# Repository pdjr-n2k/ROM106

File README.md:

# ROM106 - NMEA 2000 relay output module

**ROM106** is a specialisation of
[NOP100](https://github.com/preeve9534/NOP100)
and implements a six channel NMEA 2000 relay output module which
presents on the host NMEA bus as a switchbank device with Class
Code 30 (Electrical Distribution) and Function Code 140 (Load
Controller).

The module transmits PGN 127501 Binary Status Report messages and
responds to PGN 127502 Switch Bank Control messages addressed to
the module's instance number.

The module is powered from the host NMEA bus and has an LEN of 0.5.

## Relay outputs

**ROM106**'s relay output sub-system consists of six bistable relays
with zero-volt common (CO), normally-open (NO) and normally-closed (NC)
terminals availble for the connection of external circuits.

Relay connections are rated for a maximum of 5A at up to 220VAC
or 30VDC.

## Relay operation and status reporting

**ROM106** accepts PGN 127502 Switch Bank Control messages addressed
to its module's instance number, updating its relay outputs to the
requested states.
Operation of individual relays is queued so that any request for state
change of multiple relays cannot result in a possibly problematic
concurrent relay switching load.

The module reports module status by regularly broadcasting a PGN 127501
Binary Status Report message.
Additionally, a report is broadcast immediately following the receipt and
handling of a PGN 127502 Switch Bank Control message.
The regular transmission interval can be configured by the user.

## Module configuration

**ROM106** understands the following configuration parameters.

| Address | Name                         | Default value | Description |
| :---:   | :---                         | :---:         | :--- |
| 0x01    | MODULE INSTANCE NUMBER       | 0xFF          | Used as a unique identifier for this switchbank. Must be set by the user to a value between 0 and 252 before the module will transmit status reports. |
| 0x02    | PGN 127501 TRANSMIT INTERVAL | 0x04          | Sets the basic transmit interval for broadcast of module status reports.|

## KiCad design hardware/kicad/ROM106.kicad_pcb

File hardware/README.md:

# TSENSE 1.0 Prototype Hardware

This microcontroller-based design uses just a handful of components
to implement an 8-channel NMEA 2000 temperature sensor module which
is powered from the host NMEA 2000 bus and draws around 50mA of
current at a nominal 12VDC with all eight sensor channels in use.
This equates to an NMEA bus load of less that 1 LEN.

The module supports
[National Semiconductor LM335Z](https://www.switchelectronics.co.uk/pub/media/pdf/LM335Z.pdf)
precision temperature sensors connected through a two-wire interface.
The module cannot be used with resistance or current-loop sensors.

The module has a simple user configuration interface consisting of a
DIP switch, momentary push-button and LED outputs.
A separate LED indicates module operating state.

## Active components

| Element         | Device |
|:----------------|:-------|
| MCU             | [Teensy 3.2](https://www.pjrc.com/store/teensy32.html) |
| Power supply    | [Traco Power TMR 1-1211](https://tracopower.com/tmr1-datasheet/) |
| CAN transceiver | [MicroChip MCP2551](http://ww1.microchip.com/downloads/en/devicedoc/21667e.pdf) |

## Schematic design

<br clear="both"/>

## Physical design

The prototype module uses through-hole components on a 75mm square PCB
mounted in a flanged ABS enclosure.
The enclosure is machined to accommodate an NMEA cable connector and
a single 3mm LED indicator.

| Element         | Device |
|:----------------|:-------|
| Enclosure       | [RS 919-0357](https://docs.rs-online.com/960c/0900766b814af9a1.pdf) |
| NMEA connector  | [M12 5-pin connector](https://docs.rs-online.com/e3ad/0900766b8152901f.pdf) |

<br clear="both"/>

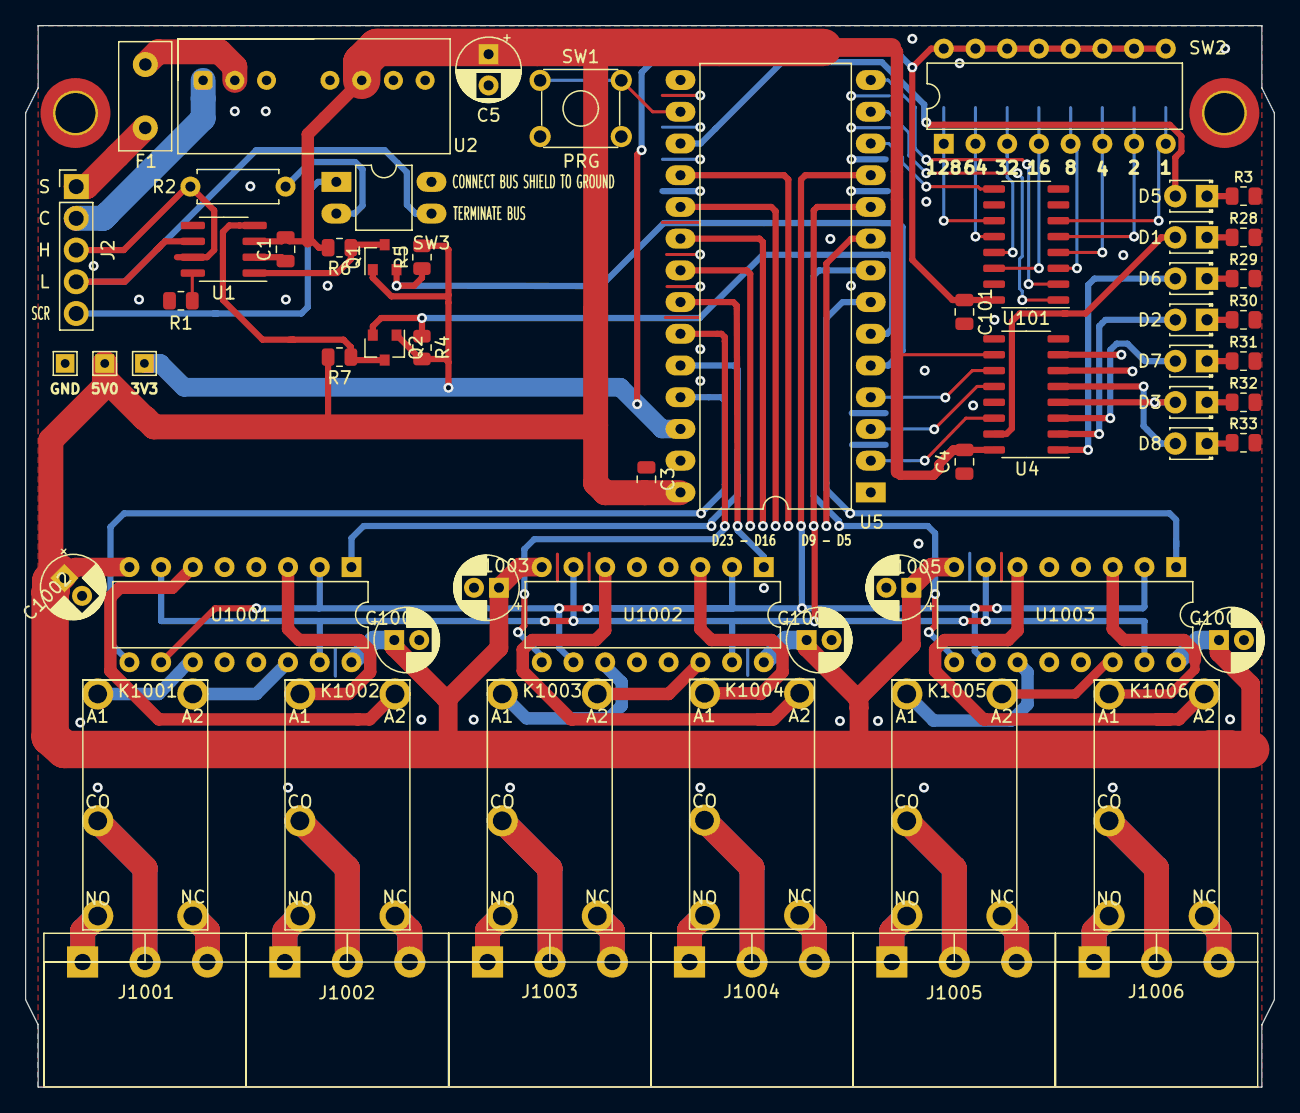
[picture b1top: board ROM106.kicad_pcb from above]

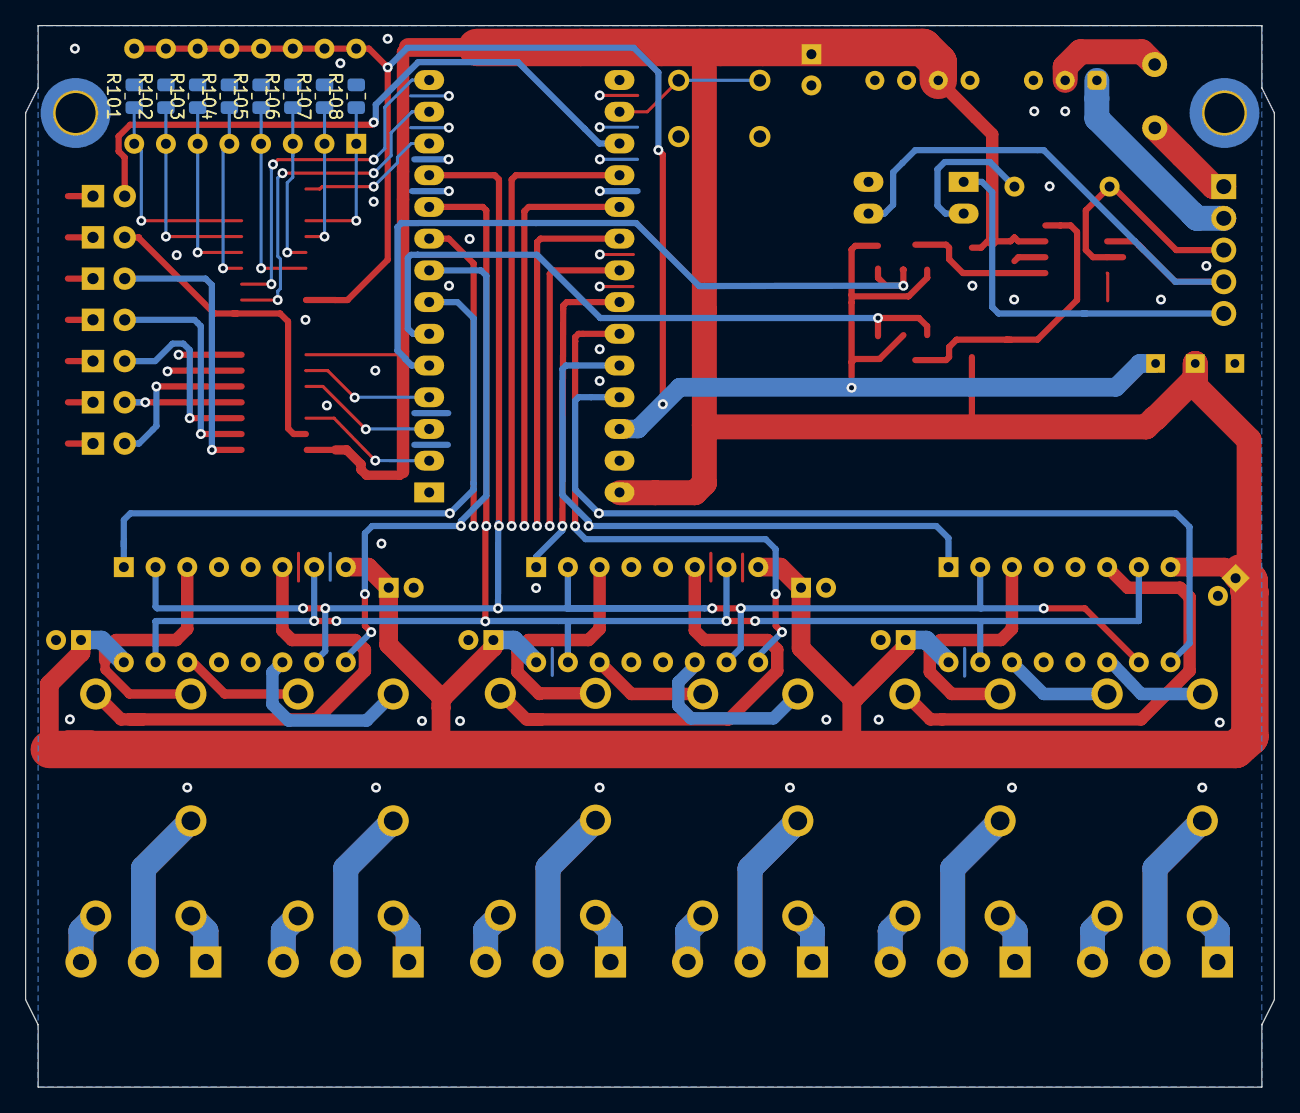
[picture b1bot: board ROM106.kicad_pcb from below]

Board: 2 copper layers, 100.0 x 85.0 mm, 68 parts (8 on the bottom side), 82 nets.

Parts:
C1, C3, C4, C101: 100nF; C_0805_2012Metric
C5: 100nF; CP_Radial_D5.0mm_P2.50mm
C1001, C1002, C1003, C1004, C1005, C1006: 100nF; CP_Radial_D5.0mm_P2.00mm
D1, D2, D3, D5, D6, D7, D8: LED; LED_D1.8mm_W3.3mm_H2.4mm
F1: 1A; Fuse_Littelfuse_395Series
J2: CAN; PinHeader_1x05_P2.54mm_Vertical
J1001, J1002, J1003, J1004, J1005, J1006: Screw_Terminal_01x03; 8971187_3_PIN_5MM_PLUGGABLE_HEADER
K1001, K1002, K1003, K1004, K1005, K1006: PE014F05
Q1, Q2: BSS138; SOT-23
R1, R101, R102, R103, R104, R105, R106, R107, R108: 4K7 0.125W; R_0805_2012Metric
R2: 120R 0.5W; R_Axial_DIN0207_L6.3mm_D2.5mm_P7.62mm_Horizontal
R3, R28, R29, R30, R31, R32, R33: 560R; R_0805_2012Metric
R4, R5, R6, R7: 10K 0.125W; R_0805_2012Metric
SW1: PRG; SW_TH_Tactile_Omron_B3F-10xx
SW2: INSTANCE; DIP-16_W7.62mm
SW3: BUS; DIP-4_W7.62mm_LongPads
TEST 5V0, TEST 5V0#2: TestPoint_THTPad_1.5x1.5mm_Drill0.7mm
U1: MCP2551-I-P; SOIC-8_3.9x4.9mm_P1.27mm
U2: TMR-2-2411; TMR_2411
U4: 74HCT595; SO-16_3.9x9.9mm_P1.27mm
U5: Teensy_4.0; DIP-28_W15.24mm_LongPads
U101: 74HC165; SO-16_3.9x9.9mm_P1.27mm
U1001, U1002, U1003: L293D; DIP-16_W7.62mm

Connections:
+3V3: C101.1, Q1.1, Q2.1, R4.2, R5.2, SW2.9, SW2.10, SW2.11, SW2.12, SW2.13, SW2.14, SW2.15, SW2.16, TEST 5V0.1, U5.26, U101.16
+5V: C1.1, C3.1, C4.1, C5.1, C1001.1, C1002.1, C1003.1, C1004.1, C1005.1, C1006.1, R6.2, R7.2, TEST 5V0#2.1, U1.3, U2.6, U4.10, U4.16, U5.28, U1001.8, U1001.16, U1002.8, U1002.16, U1003.8, U1003.16
/CAN_RX: Q2.2, R4.1, U5.6
/CAN_TX: Q1.2, R5.1, U5.5
/D5: U5.7, U1003.1
/D6: U5.8, U1003.9
/D8: U5.10, U1001.7, U1001.15, U1002.7, U1002.15, U1003.7, U1003.15
/D9: U5.11, U1001.2, U1001.10, U1002.2, U1002.10, U1003.2, U1003.10
/D20: U5.22, U1002.1
/D21: U5.23, U1002.9
/D22: U5.24, U1001.1
/D23: U5.25, U1001.9
/PISO_CP: U5.14, U101.2
/PISO_PL: U5.13, U101.1
/PISO_Q7: U5.12, U101.9
/PRG: SW1.1, SW1.2, U5.16
/SIPO_CLOCK: U4.11, U5.4
/SIPO_DATA: U4.14, U5.2
/SIPO_LATCH: U4.12, U5.3
GND: C1.2, C3.2, C4.2, C5.2, C101.2, C1001.2, C1002.2, C1003.2, C1004.2, C1005.2, C1006.2, R1.1, R3.2, R28.2, R29.2, R30.2, R31.2, R32.2, R33.2, R101.2, R102.2, R103.2, R104.2, R105.2, R106.2, R107.2, R108.2, SW1.3, SW1.4, SW3.4, U1.2, U2.7, U4.8, U4.13, U5.1, U5.27, U101.8, U101.10, U101.15, U1001.4, U1001.5, U1001.12, U1001.13, U1002.4, U1002.5, U1002.12, U1002.13, U1003.4, U1003.5, U1003.12, U1003.13
unnamed: D1.1, R28.1
unnamed: D1.2, U4.15
unnamed: D2.1, R30.1
unnamed: D2.2, U4.2
unnamed: D3.1, R32.1
unnamed: D3.2, U4.4
unnamed: D5.1, R3.1
unnamed: D5.2, U5.17
unnamed: D6.1, R29.1
unnamed: D6.2, U4.1
unnamed: D7.1, R31.1
unnamed: D7.2, U4.3
unnamed: D8.1, R33.1
unnamed: D8.2, U4.5
unnamed: F1.1, J2.1
unnamed: F1.2, U2.2
unnamed: J2.2, U2.1
unnamed: J2.3, R2.1, U1.7
unnamed: J2.4, SW3.3, U1.6
unnamed: J2.5, SW3.1
unnamed: J1001.1, K1001.14
unnamed: J1001.2, K1001.7
unnamed: J1001.3, K1001.1
unnamed: J1002.1, K1002.14
unnamed: J1002.2, K1002.7
unnamed: J1002.3, K1002.1
unnamed: J1003.1, K1003.14
unnamed: J1003.2, K1003.7
unnamed: J1003.3, K1003.1
unnamed: J1004.1, K1004.14
unnamed: J1004.2, K1004.7
unnamed: J1004.3, K1004.1
unnamed: J1005.1, K1005.14
unnamed: J1005.2, K1005.7
unnamed: J1005.3, K1005.1
unnamed: J1006.1, K1006.14
unnamed: J1006.2, K1006.7
unnamed: J1006.3, K1006.1
unnamed: K1001.2, U1001.14
unnamed: K1001.6, U1001.11
unnamed: K1002.2, U1001.6
unnamed: K1002.6, U1001.3
unnamed: K1003.2, U1002.14
unnamed: K1003.6, U1002.11
unnamed: K1004.2, U1002.6
unnamed: K1004.6, U1002.3
unnamed: K1005.2, U1003.14
unnamed: K1005.6, U1003.11
unnamed: K1006.2, U1003.6
unnamed: K1006.6, U1003.3
unnamed: Q1.3, R6.1, U1.1
unnamed: Q2.3, R7.1, U1.4
unnamed: R1.2, U1.8
unnamed: R2.2, SW3.2
unnamed: R101.1, SW2.8, U101.6
unnamed: R102.1, SW2.7, U101.5
unnamed: R103.1, SW2.6, U101.4
unnamed: R104.1, SW2.5, U101.3
unnamed: R105.1, SW2.4, U101.14
unnamed: R106.1, SW2.3, U101.13
unnamed: R107.1, SW2.2, U101.12
unnamed: R108.1, SW2.1, U101.11

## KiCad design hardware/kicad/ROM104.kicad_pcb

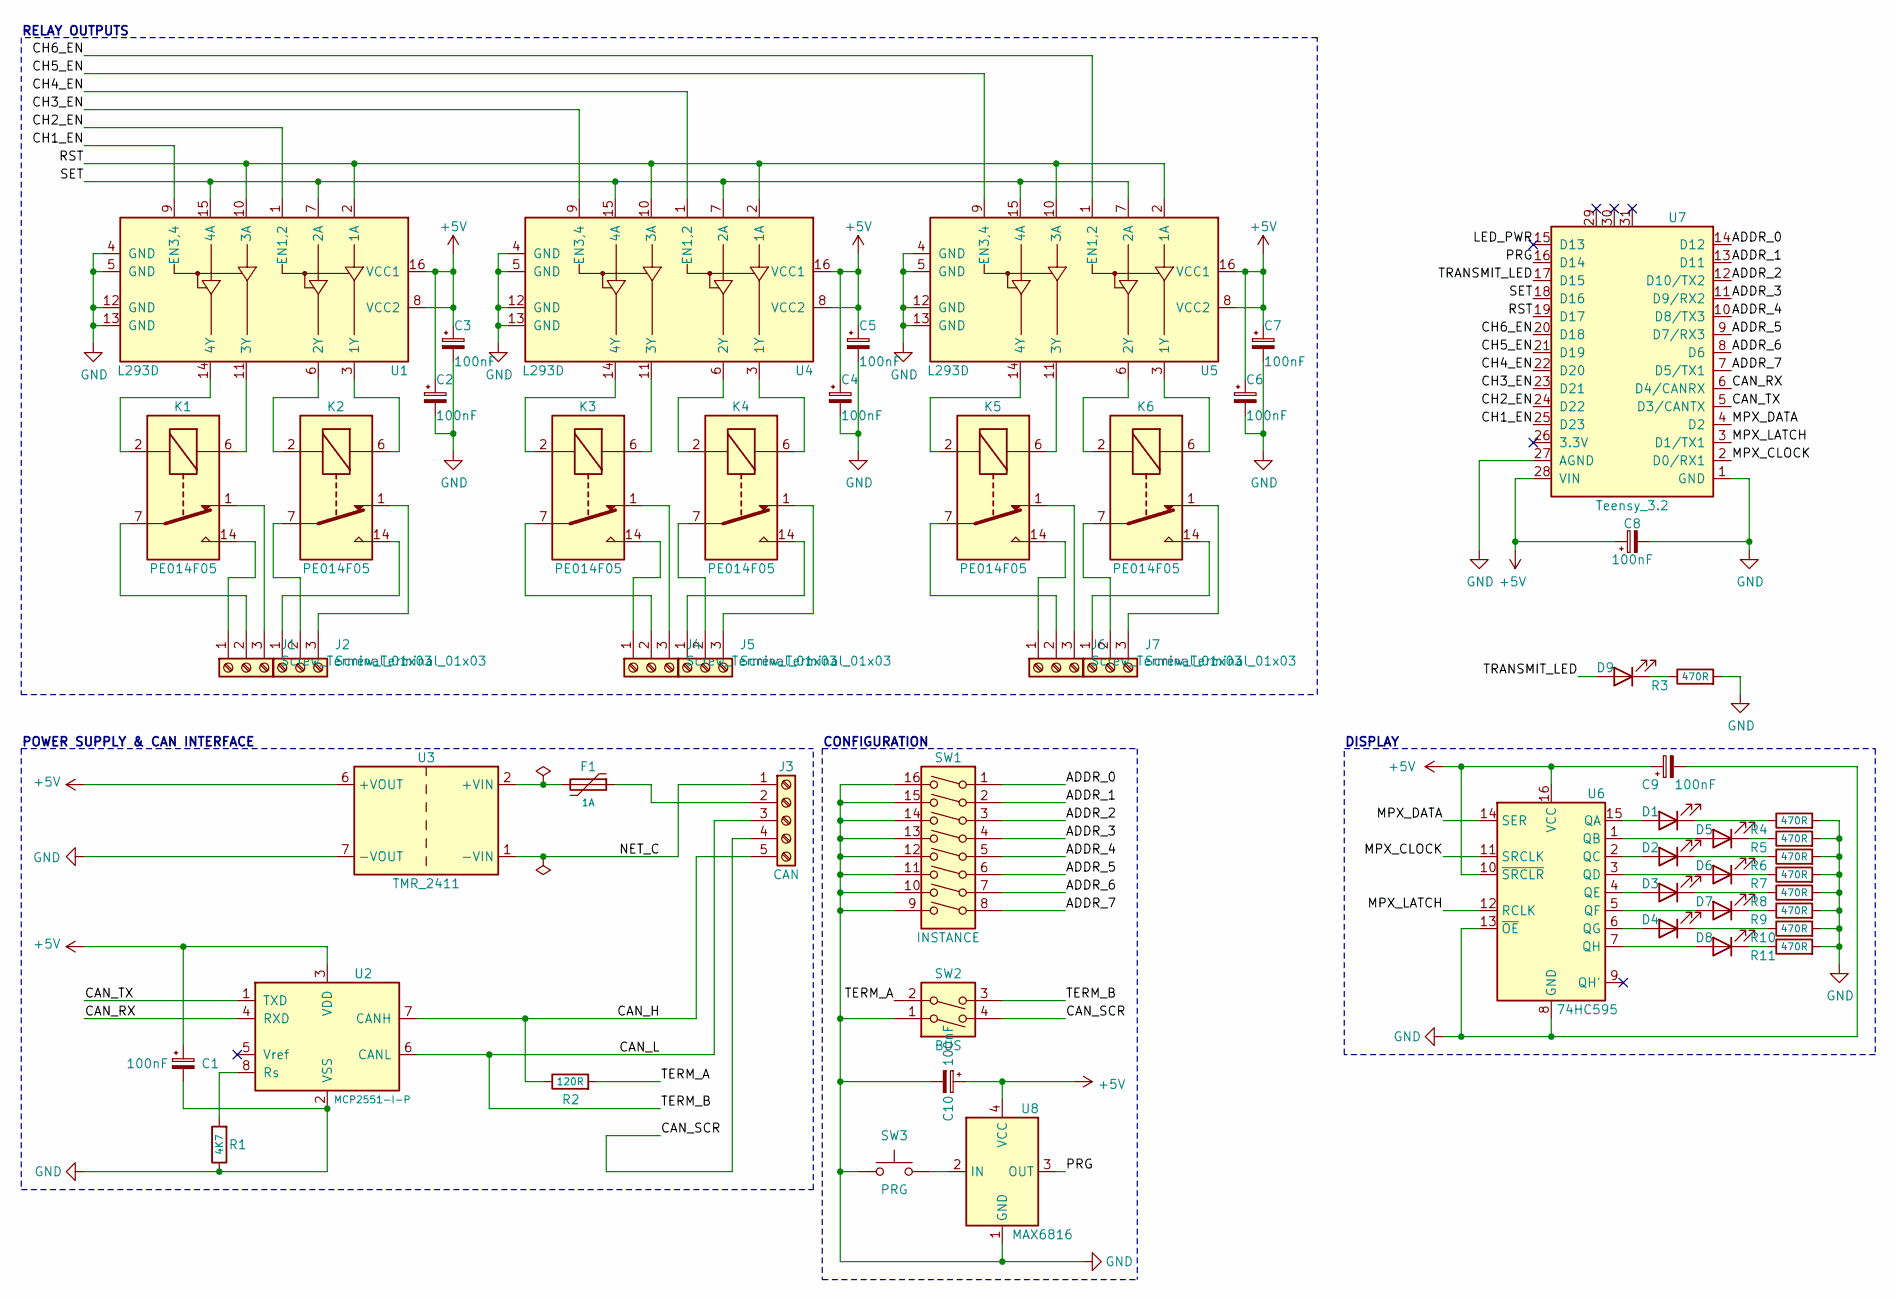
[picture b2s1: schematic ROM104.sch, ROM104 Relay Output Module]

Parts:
C1, C2, C3, C4, C5, C6, C7, C8, C9, C10: 100nF; CP_Radial_D5.0mm_P2.00mm
D1, D2, D3, D4, D5, D6, D7, D8, D9: LED; LED_D1.8mm_W3.3mm_H2.4mm
F1: 1A; Fuse_Littelfuse_395Series
J1, J2, J4, J5, J6, J7: Screw_Terminal_01x03; 8971187_3_PIN_5MM_PLUGGABLE_HEADER
J3: CAN; PinHeader_1x05_P2.54mm_Vertical
K1, K2, K3, K4, K5, K6: PE014F05
R1: 4K7; R_Axial_DIN0207_L6.3mm_D2.5mm_P2.54mm_Vertical
R2: 120R; R_Axial_DIN0207_L6.3mm_D2.5mm_P7.62mm_Horizontal
R3, R4, R5, R6, R7, R8, R9, R10, R11: 470R; R_Axial_DIN0207_L6.3mm_D2.5mm_P2.54mm_Vertical
SW1: INSTANCE; DIP-16_W7.62mm
SW2: BUS; DIP-4_W7.62mm_LongPads
SW3: PRG; PCB_PUSH_BUTTON
U1, U4, U5: L293D; DIP-16_W7.62mm
U2: MCP2551-I-P; DIP-8_W7.62mm
U3: TMR_2411
U6: 74HC595; DIP-16_W7.62mm_Socket_LongPads
U7: Teensy_3.2; DIP-28_W15.24mm_LongPads
U8: MAX6816; SOT-143

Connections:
+5V: C1.1, C2.1, C3.1, C4.1, C5.1, C6.1, C7.1, C8.1, C9.1, C10.1, U1.8 (VCC2), U1.16 (VCC1), U2.3 (VDD), U3.6 (+VOUT), U4.8 (VCC2), U4.16 (VCC1), U5.8 (VCC2), U5.16 (VCC1), U6.10 (~SRCLR), U6.16 (VCC), U7.28 (VIN), U8.4 (VCC); also elsewhere on the board
/ADDR_0: SW1.1, U7.14 (D12)
/ADDR_1: SW1.2, U7.13 (D11)
/ADDR_2: SW1.3, U7.12 (D10/TX2)
/ADDR_3: SW1.4, U7.11 (D9/RX2)
/ADDR_4: SW1.5, U7.10 (D8/TX3)
/ADDR_5: SW1.6, U7.9 (D7/RX3)
/ADDR_6: SW1.7, U7.8 (D6)
/ADDR_7: SW1.8, U7.7 (D5/TX1)
/CAN_H: J3.5, R2.1, U2.7 (CANH)
/CAN_L: J3.3, SW2.3, U2.6 (CANL)
/CAN_RX: U2.4 (RXD), U7.6 (D4/CANRX)
/CAN_SCR: J3.4, SW2.4
/CAN_TX: U2.1 (TXD), U7.5 (D3/CANTX)
/CH1_EN: U1.9 (EN3,4), U7.25 (D23)
/CH2_EN: U1.1 (EN1,2), U7.24 (D22)
/CH3_EN: U4.9 (EN3,4), U7.23 (D21)
/CH4_EN: U4.1 (EN1,2), U7.22 (D20)
/CH5_EN: U5.9 (EN3,4), U7.21 (D19)
/CH6_EN: U5.1 (EN1,2), U7.20 (D18)
/LED_PWR: U7.15 (D13)
/MPX_CLOCK: U6.11 (SRCLK), U7.2 (D0/RX1)
/MPX_DATA: U6.14 (SER), U7.4 (D2)
/MPX_LATCH: U6.12 (RCLK), U7.3 (D1/TX1)
/NET_C: J3.1, U3.1 (-VIN)
/PRG: U7.16 (D14), U8.3 (OUT)
/RST: U1.2 (1A), U1.10 (3A), U4.2 (1A), U4.10 (3A), U5.2 (1A), U5.10 (3A), U7.19 (D17)
/SET: U1.7 (2A), U1.15 (4A), U4.7 (2A), U4.15 (4A), U5.7 (2A), U5.15 (4A), U7.18 (D16)
/TERM_A: R2.2, SW2.2
/TRANSMIT_LED: D9.2 (A), U7.17 (D15)
GND: C1.2, C2.2, C3.2, C4.2, C5.2, C6.2, C7.2, C8.2, C9.2, C10.2, R1.1, R3.2, R4.2, R5.2, R6.2, R7.2, R8.2, R9.2, R10.2, R11.2, SW1.9, SW1.10, SW1.11, SW1.12, SW1.13, SW1.14, SW1.15, SW1.16, SW2.1, SW3.1, U1.4 (GND), U1.5 (GND), U1.12 (GND), U1.13 (GND), U2.2 (VSS), U3.7 (-VOUT), U4.4 (GND), U4.5 (GND), U4.12 (GND), U4.13 (GND), U5.4 (GND), U5.5 (GND), U5.12 (GND), U5.13 (GND), U6.8 (GND), U6.13 (~OE), U7.1 (GND), U7.27 (AGND), U8.1 (GND); also elsewhere on the board
unnamed: D1.1 (K), R4.1
unnamed: D1.2 (A), U6.15 (QA)
unnamed: D2.1 (K), R6.1
unnamed: D2.2 (A), U6.2 (QC)
unnamed: D3.1 (K), R8.1
unnamed: D3.2 (A), U6.4 (QE)
unnamed: D4.1 (K), R10.1
unnamed: D4.2 (A), U6.6 (QG)
unnamed: D5.1 (K), R5.1
unnamed: D5.2 (A), U6.1 (QB)
unnamed: D6.1 (K), R7.1
unnamed: D6.2 (A), U6.3 (QD)
unnamed: D7.1 (K), R9.1
unnamed: D7.2 (A), U6.5 (QF)
unnamed: D8.1 (K), R11.1
unnamed: D8.2 (A), U6.7 (QH)
unnamed: D9.1 (K), R3.1
unnamed: F1.1, J3.2
unnamed: F1.2, U3.2 (+VIN)
unnamed: J1.1, K1.14
unnamed: J1.2, K1.7
unnamed: J1.3, K1.1
unnamed: J2.1, K2.14
unnamed: J2.2, K2.7
unnamed: J2.3, K2.1
unnamed: J4.1, K3.14
unnamed: J4.2, K3.7
unnamed: J4.3, K3.1
unnamed: J5.1, K4.14
unnamed: J5.2, K4.7
unnamed: J5.3, K4.1
unnamed: J6.1, K5.14
unnamed: J6.2, K5.7
unnamed: J6.3, K5.1
unnamed: J7.1, K6.14
unnamed: J7.2, K6.7
unnamed: J7.3, K6.1
unnamed: K1.2, U1.14 (4Y)
unnamed: K1.6, U1.11 (3Y)
unnamed: K2.2, U1.6 (2Y)
unnamed: K2.6, U1.3 (1Y)
unnamed: K3.2, U4.14 (4Y)
unnamed: K3.6, U4.11 (3Y)
unnamed: K4.2, U4.6 (2Y)
unnamed: K4.6, U4.3 (1Y)
unnamed: K5.2, U5.14 (4Y)
unnamed: K5.6, U5.11 (3Y)
unnamed: K6.2, U5.6 (2Y)
unnamed: K6.6, U5.3 (1Y)
unnamed: R1.2, U2.8 (Rs)
unnamed: SW3.2, U8.2 (IN)

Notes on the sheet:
POWER SUPPLY & CAN INTERFACE
CONFIGURATION
DISPLAY
RELAY OUTPUTS

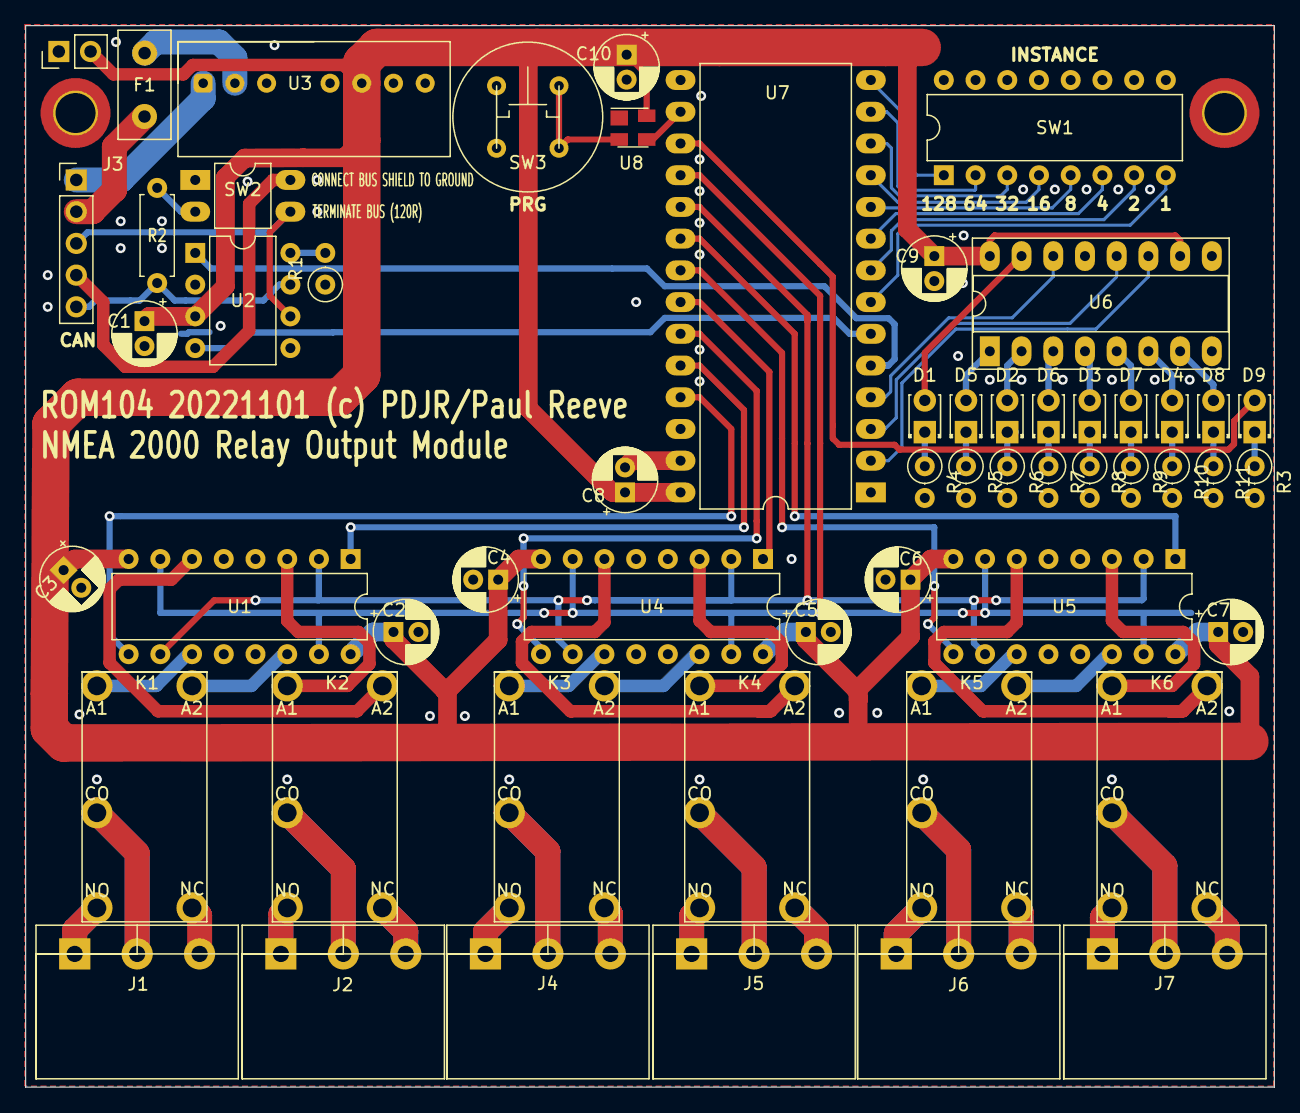
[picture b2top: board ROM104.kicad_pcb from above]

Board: 2 copper layers, 100.0 x 85.0 mm, 56 parts (0 on the bottom side), 81 nets.

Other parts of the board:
TEST: PinHeader_1x02_P2.54mm_Vertical

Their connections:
+5V: TEST.2; also elsewhere on the board
GND: TEST.1; also elsewhere on the board

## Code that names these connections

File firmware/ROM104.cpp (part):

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 * GPIO pin definitions for the Teensy 3.2 MCU and some collections
 * that can be used as array initialisers
 */
#define GPIO_MPX_CLOCK 0
#define GPIO_MPX_LATCH 1
#define GPIO_MPX_DATA 2
#define GPIO_CAN_TX 3
#define GPIO_CAN_RX 4
#define GPIO_INSTANCE_BIT0 5
#define GPIO_INSTANCE_BIT1 6 
#define GPIO_INSTANCE_BIT2 7
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#define GPIO_INSTANCE_BIT6 11
#define GPIO_INSTANCE_BIT7 12
#define GPIO_POWER_LED 13
#define GPIO_PRG 14
#define GPIO_RELAY6_ENABLE 16
#define GPIO_RELAY5_ENABLE 17
#define GPIO_RELAY4_ENABLE 18
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#define GPIO_RELAY_SET 22
#define GPIO_RELAY_RST 23
#define GPIO_INSTANCE_PINS { GPIO_INSTANCE_BIT0, GPIO_INSTANCE_BIT1, GPIO_INSTANCE_BIT2, GPIO_INSTANCE_BIT3, GPIO_INSTANCE_BIT4, GPIO_INSTANCE_BIT5, GPIO_INSTANCE_BIT6, GPIO_INSTANCE_BIT7 }
#define GPIO_INPUT_PINS { GPIO_PRG, GPIO_INSTANCE_BIT0, GPIO_INSTANCE_BIT1, GPIO_INSTANCE_BIT2, GPIO_INSTANCE_BIT3, GPIO_INSTANCE_BIT4, GPIO_INSTANCE_BIT5, GPIO_INSTANCE_BIT6, GPIO_INSTANCE_BIT7 }
#define GPIO_OUTPUT_PINS { GPIO_POWER_LED, GPIO_MPX_CLOCK, GPIO_MPX_LATCH, GPIO_MPX_DATA, GPIO_RELAY1_ENABLE, GPIO_RELAY2_ENABLE, GPIO_RELAY3_ENABLE, GPIO_RELAY4_ENABLE, GPIO_RELAY5_ENABLE, GPIO_RELAY6_ENABLE, GPIO_RELAY_SET, GPIO_RELAY_RST }

/**********************************************************************
 * DEVICE INFORMATION
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/**********************************************************************
 * LED_DISPLAY parallel buffer IC interface for operating LEDs.
 */
B74HC595 LED_DISPLAY (getLedStatus, LED_UPDATE_INTERVAL, GPIO_MPX_DATA, GPIO_MPX_CLOCK, GPIO_MPX_LATCH);

/**********************************************************************
 * Whether or not to enable operation of the transmit LED.
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  delay(DEBUG_SERIAL_START_DELAY);
  #endif

  // Set the mode of all digital GPIO pins.
  int ipins[] = GPIO_INPUT_PINS;
  int opins[] = GPIO_OUTPUT_PINS;
  for (unsigned int i = 0 ; i < ELEMENTCOUNT(ipins); i++) pinMode(ipins[i], INPUT_PULLUP);
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  NMEA2000.Open();

  // Attach interrupt service routine to PRG button
  attachInterrupt(digitalPinToInterrupt(GPIO_PRG), isr, RISING);
}

/**********************************************************************
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 * loop.
 * 
 * The function will execute each RELAY_OPERATION_QUEUE_INTERVAL and
 * it is important that this constant is set to a value equal to or
 * greater than the minimum operating signal hold period of the
 * physical relays installed on the host PCB. For most latching
 * relays this will be around 20ms.
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 * indicates whether the channel should be turned on (set) or turned
 * off (reset).
 * 
 * The function sets up H-bridge SET and RST GPIOs appropriately and
 * then switches on the selected channel's ENABLE GPIO, thus energising
 * the associated relay coil. A call is made to request transmission of
 * an NMEA message signalling the state change.
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
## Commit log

2022-09-10 Getting started
2022-09-10 Getting going
2022-09-10 Getting closer
2022-09-11 In progress
2022-09-11 Stuff
2022-09-11 Callback stuff
2022-09-11 Shakedown
2022-09-11 Tweaks
2022-09-12 First compile
2022-09-17 Add PCB silk labels
2022-09-17 PCB silk update
2022-09-18 Switch PSU to 2W
2022-09-18 Revise silk screen
2022-09-18 Change relay terminal
2022-09-18 PCB tweak
2022-09-19 Change resistor footprints
2022-09-19 Restore 1/4W resistor footprints
2022-09-20 Update PCB
2022-09-25 PCB resize
2022-09-25 New PCB layout
2022-09-26 Tidy up.
2022-09-26 Add PRG switch
2022-09-27 PCB update
2022-09-27 Revised PCB
2022-09-27 README update.
2022-09-28 Update README.md
    Add debouncer.
2022-09-28 Add PRG debounce
2022-10-05 Refactor
2022-10-08 New libraries
2022-10-10 Create firmware-factory.code-workspace
2022-10-25 PCB reroute
2022-10-27 Update fp-lib-table
2022-10-29 Tweak
2022-11-07 PCB reshape
2022-11-07 Tidy up
2022-12-19 Redraw PCB
2022-12-20 Relay PCB
2022-12-20 Various.
2022-12-21 New code
2022-12-21 Add configureModuleInstance
2022-12-21 Fix pointer
2022-12-24 PCB layout
2022-12-24 Update to new NOP100 core
2022-12-27 Update config
2022-12-27 Comments
2023-01-08 Refactor
    Prepare for enhanced firmware.

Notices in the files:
firmware/ROM104.cpp:
Copyright (c) 2021-22 Paul Reeve <preeve@pdjr.eu>
